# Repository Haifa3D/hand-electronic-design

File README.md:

# Oded Hand Electrical Design  

This project is a sub-project of Haifa3D Robotic Hand.
In this project, we present the electrical design of the Oded Hand – a 3D printed robotic hand with five micro-DC motors. 
The aim of this design is to be low cost, accessible, easy to assemble, robust and lightweight.  

## Design Description  
The Oded Hand can perform a variety of user-defined hand configurations using an autonomous adaptive grip along with a variety of configurable grip force levels.
The electrical design consists of four fingers with four different tendon-driven mechanisms actuated by four micro-DC motors, a passive thumb which magnetically locks in two discrete positions and wrist rotation driven by planetary gears and a DC motor. 

The electronic system consists of:
* The circuit and controller code
* The circuit housing and socket
* The batteries housing

The electronic system presented here also allows a Bluetooth communication between the Hand and your phone for settings configuration and a modular sensors control (see our [Mobile App](https://github.com/Haifa3D/haifa3d-hand-app)). For more details on how to manufacture and assemble the hand, please check out our [Mechanical Design](https://github.com/Haifa3D/hand-mechanical-design). 

## Who can benefit from this Design?  
The design is suitable for users with transradial amputation (below the elbow).
We welcome any new developers to enhance our design or to use the Oded Hand as a simulator for your new sensors/algorithms/methods that would potentially help users with controling their prosthetic hand.

## Design Files and Versions  
The STL files for the battery housing and the circuit housing can be found [here](CAD_files). The gerber files of the PCB design can be found [here](gerber_files/CAMOutputs) as well as the [schematic and layout](docs). The EAGLE files for modifying the board can be found [here](EAGLE_files). The Arduino code for the controller can be downloaded from [here](controller_software/Oded_Hand_board7_app2_4_6).

## Getting Started:
To build the electronic system for Oded Hand you will need a basic knowledge of soldering and the following componenets: 

| Component Name | Quantity | Value | links |
| --- | --- | --- | --- |
| ESP32 DEVKIT V1| 1 | - | [pinouts](https://randomnerdtutorials.com/esp32-pinout-reference-gpios/) [aliexpress](https://www.aliexpress.com/item/4000071762309.html?spm=a2g0s.9042311.0.0.64074c4du1Hh8a) |
| DRV8833 Pololu breakout board | 3 | - | [pololu](https://www.pololu.com/product/2130) | 
| micro metal dc motor | 5 | MP/LP, 100-200 RPM x 4, 30RPM x 1 | [pololu](https://www.pololu.com/product/2360), [aliexpress](https://www.aliexpress.com/item/1005003482247510.html?spm=a2g0o.productlist.main.5.70497ad7QQdXAy&algo_pvid=51493eeb-ec56-46bd-8e1c-2290c1519572&algo_exp_id=51493eeb-ec56-46bd-8e1c-2290c1519572-2&pdp_npi=3%40dis%21USD%212.08%211.44%21%21%21%21%21%40212279b716866852206383478d075c%2112000025985331271%21sea%21IL%211746261860&curPageLogUid=CFjbpVP4CzBR) | 
| IDC Connector flat cable | 1 x Right Angle Male + 1 x Female | 5x2 pins | [aliexpress RA Male](https://www.aliexpress.com/item/32841491672.html?spm=a2g0s.9042311.0.0.64074c4du1Hh8a), [aliexpress Female](https://www.aliexpress.com/item/32848157974.html?spm=a2g0s.9042311.0.0.64074c4du1Hh8a) |
| KF2510 Connector | 1 x Right Angle Male + 1 x Female  | 2 pins, 2.54mm pitch | [aliexpress](https://www.aliexpress.com/item/4000229650832.html?spm=a2g0o.productlist.0.0.580e59f7kz5W45&algo_pvid=70b8595e-d2a1-41e6-90ef-ca210f686aeb&algo_expid=70b8595e-d2a1-41e6-90ef-ca210f686aeb-20&btsid=2100bb4c16102253905804689e5410&ws_ab_test=searchweb0_0,searchweb201602_,searchweb201603_) |
| Right Angle SPDT Rocker Switch | 1 | for 3 Amp | [aliexpress](https://www.aliexpress.com/i/33009610601.html) |
| RGB LED Common Cathode | 1 | Common Cathode | [aliexpress](https://www.aliexpress.com/item/32666259962.html?spm=a2g0s.9042311.0.0.27424c4dhW29h7) |
| Li-ion 18650 battery | 2-4 | >2500mAh | [aliexpress](https://www.aliexpress.com/item/4000838767077.html?spm=a2g0o.detail.1000013.7.89c81382J9Ew7p&gps-id=pcDetailBottomMoreThisSeller&scm=1007.13339.291025.0&scm_id=1007.13339.291025.0&scm-url=1007.13339.291025.0&pvid=9ae560ff-e9e4-4dd9-a998-aac4cd26bcfe&_t=gps-id:pcDetailBottomMoreThisSeller,scm-url:1007.13339.291025.0,pvid:9ae560ff-e9e4-4dd9-a998-aac4cd26bcfe,tpp_buckets:668%232846%238116%232002&pdp_npi=3%40dis%21USD%213.75%212.62%21%21%21%21%21%402103244816864283632677463e15d8%2110000008755087021%21rec%21IL%211746261860) |
| battery Spring Contact Plate For AA AAA Battery | 4 | =< 12x12 mm |[aliexpress](https://www.aliexpress.com/item/1005001308633882.html?spm=a2g0o.detail.1000014.4.231d5d481DZZjH&gps-id=pcDetailBottomMoreOtherSeller&scm=1007.33416.205061.0&scm_id=1007.33416.205061.0&scm-url=1007.33416.205061.0&pvid=e82892c5-870e-4ffe-bb26-f0607f6946e2&_t=gps-id:pcDetailBottomMoreOtherSeller,scm-url:1007.33416.205061.0,pvid:e82892c5-870e-4ffe-bb26-f0607f6946e2,tpp_buckets:668%230%23131923%2347_668%23888%233325%235_23416%230%23205061%2320_23416%234721%2321967%23165_23416%234722%2321972%2310_668%232846%238112%231997_668%232717%237562%23468_668%231000022185%231000066059%230_668%233422%2315392%23668_4452%230%23211409%230_4452%233474%2315675%2389_4452%234862%2322449%23497_4452%233098%239599%23887_4452%235108%2323442%23113_4452%233564%2316062%236) |
| Resistors (through hole) |  | 1x2M, 1x1M, 1x10K, 2x100ohm, 1x150ohm, 5x(0.5-0.7)ohm | |

### Instructions
* send the [gerber files](gerber_files/CAMOutputs) for manufacturing at one of the availble online services (for instance, check out [PCBWay](https://www.pcbway.com/))

* order all the components from the list above.

* Cut the drv8833 according to [Pololu's instructions](https://www.pololu.com/product/2130) and check that both of the Isense pins are NOT grounded:
 
[image was taken from Pololu website]

*Tip: cut with a sharp knife the two lines, check with multimeter the resistence between AISEN/BISEN and GND. should be ~100Mohms*

* solder the headers of the drv8833 so the chip faces upward:
 
[image was taken from Pololu website]

* Solder the top side of the board (all components except the ESP32 and resistors)

*Tip: start from the led(the smallest pitch) --> drivers (drv8833)-->connectors --> button --> Switch

* Check all connections with a multimeter, to make sure everything was soldered correctly. Then cut all the pins so when you insert the esp32 controller to the bottom part nothing touches the controller. 

* Upload the [arduino code](controller_software/Oded_Hand_board7_app2_4_6) to the esp32 or an empty code, and only then solder the esp32 and the resistors (making sure there is no previous code that might cause problem to the component when it turned on). For the resistors: 1M and 2M for the voltage divider, 10K for the button, 2x100 and 1x150 ohm for the LEDs, 5x0.5ohm for the Rsense (you can use also 0.7 ohm)

After you complete the PCB assembly of Oded's Hand, please refer to the [Mechanical Design](https://github.com/Haifa3D/hand-mechanical-design) to assemble the mechanical parts of Oded's Hand. If you have already assembled the mechanical and the electrical parts, you are welcome to check out our [Mobile App](https://github.com/Haifa3D/haifa3d-hand-app) to refine the controller parameters and to define your favorite hand movements.

### **If it is the first time you are using the controller - download our [Mobile App](https://play.google.com/store/apps/details?id=com.gjung.haifa3d), connect to the hand, go to configuration and click on RESET Configuration and RESET Presets before any other action.**

## The Controller Software (Arduino code):
The code can be found [here](controller_software/Oded_Hand_board7_app2_4_6)

All installation instruction can be found in the code.

In general:

*working with Arduino IDE on ESP32:*

*https://randomnerdtutorials.com/installing-the-esp32-board-in-arduino-ide-windows-instructions/*

*Board Manager: esp32 by Espressif Systems 1.0.6~*

*Arduino IDE supported version ~1.8.15*

*install the following libraries:*

*ESP32 AnalogWrite by ERROUAGUY 0.1.0*

*ESP32 BLE Arduino Kolban/Krempa 1.0.1*

## The Circuit Housing and Socket
[Here](hand-electronic-design/CAD_files/circuit_housing), you can find the CAD of the circuit itself, the housing of the circuit top and bottom parts and the socket design we are using.
The socket is basically a flat surface which can be thermoformed and adjusted to fit the user arm. Usually the important measurements are the perimeter and length of the user's arm.

*Recommendation, merge the bottom part of the circuit housing into your socket design and print it as one part. If your socket design is based on thermoforming, heat the inner part of the socket so the bottom part of the circuit housing will not get deformed*.

To assemble the circuit housing you will need **3 x M2.5 5-8mm self tap screws** to mount the PCB to the bottom part and **2 x M2 5-6mm self tap screws** to connect the top to the bottom. To connect the hand to the socket you can use **3 x M2.5 5-8mm self tap screws** as well.

*The pictured circuit on the socket is from a previous version where we had 3 buttons on the hand instead of the mobile app for control.*

## The Batteries Housing
You can use any two connected batteries in series to power the circuit. 
To assemble your own battery pack:
* print the [batteries housing files](CAD_files/batteries_housing) (*Notice the printing orientation - the 'battery_top' should be printed so its snap is parallel to the ground*)
* make sure the batteries can slide in smoothly without getting stuck at the housing walls.
* Solder the battery Spring Contact Plate - at the 'battery-top' (the lid) the plates should be soldered to each other and at the bottom each plate should be soldered to a different wire (the maximal total current can be 2.5 amp so make sure you select a suitible wire)
* Insert the filaments to mount the contact plates to the rectangular slots at the top and bottom parts. Make sure the plates are not touching each other at the bottom part (otherwise you are going to short the batteries).
* cut the excess filaments and heat the ends (see the yellow fillaments in the image below)
* screw the bottom part to the body using two **M2 4-5mm self tap screws**
* check the connection and add a 2PIN Female KF2510 Connector to the wires.
* cut an elastic strap and sew velcro (or just buy a suitible velcro elatic strap) to fasten the Battery Pack to your upper arm. a design for backles and rings are also available at the same folder.

## So What To Do Next?
If you have developed a user interface for prosthetic hands and want to implement it on a low-cost prosthetic hand, you can communicate with our Hand in three different ways:
* if your sensors and system are on the hand and arm - you can implement your code to our controller code and solder your system to the free pins (GPIO2,12,25)
* if your system is android-based - use our [**mobile app and SDK**](https://github.com/Haifa3D/haifa3d-hand-app) to wirelessly communicate with our Hand 
* if your system is esp32-based - use the example Arduino IDE code [here](controller_software/Hand_UI_demo_BLEclient) to communicate with our Hand using the built-in BLE of the esp32 controller.
* if your system is based on Python code - use the [communication example Python code](python_communication_code/) to trigger different hand movements

## Acknowledgements:
This project was done by a group of great people and with the help and guidance of generous organizations.

*Electrical design*:  Shunit Polinsky, Yair Herbest, and Noah Bernten.

*Users Communication*: Haifa 3D – a nonprofit organization that designs and builds hands for free, founded by Yoav Medan and Yacov Malinovich.

*Resources*: The Technion - Israel Institute of Technology and special thanks to Prof. Alon Wolf and the Biorobotics and Biomechanics Lab.

## Donation:

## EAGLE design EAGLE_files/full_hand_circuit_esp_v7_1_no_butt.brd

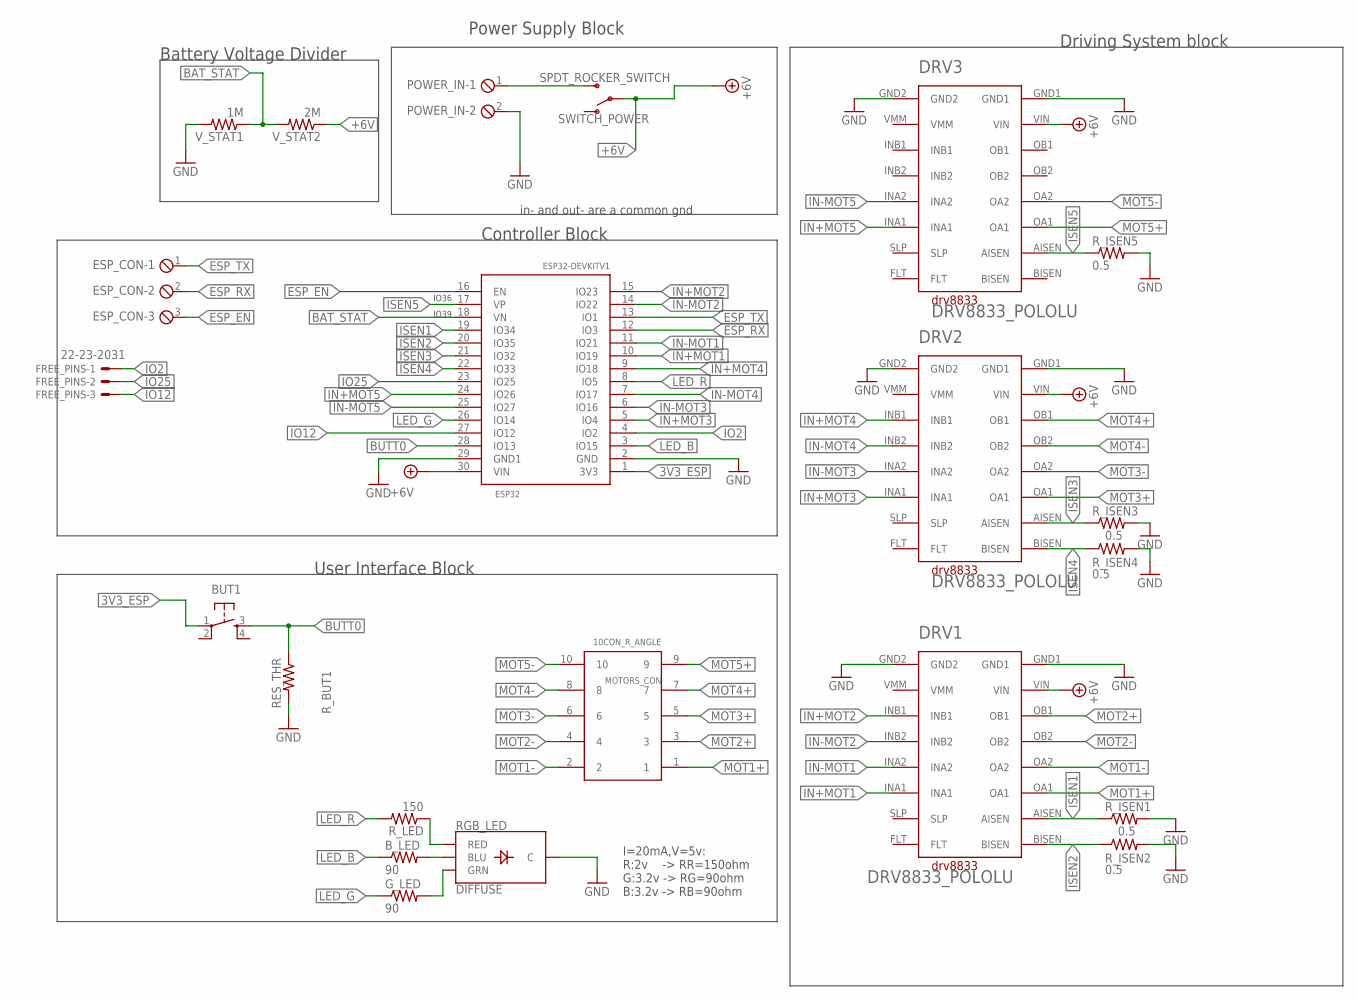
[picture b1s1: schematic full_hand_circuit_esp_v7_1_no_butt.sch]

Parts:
BUT1: PUSH_BUTTON; B3F-40XX
B_LED: 90; R_THR
DRV1, DRV2, DRV3: DRV8833_POLOLU
ESP32: ESP32DEVKITV1; ESP32-DEVKITV1
ESP_CON: MPT3; 3POL254
FREE_PINS: 22-23-2031
G_LED: 90; R_THR
MOTORS_CON: 10CON_R_ANGLE; CON10_R_ANGLE
POWER_IN: MPT2; 2POL254
RGB_LED: DIFFUSE; LED-RGB-THRU
R_BUT1: RES_THR; R_THR
R_ISEN1, R_ISEN2, R_ISEN3, R_ISEN4, R_ISEN5: 0.5; R_THR
R_LED: 150; R_THR
SWITCH_POWER: SPDT_ROCKER_SWITCH; SWITCH_SPDT_PTH_11.6X4.0MM
V_STAT1: 1M; R_THR
V_STAT2: 2M; R_THR

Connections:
3V3_ESP: BUT1.1, ESP32.1 (3V3)
+6V: DRV1.VIN, DRV2.VIN, DRV3.VIN, ESP32.30 (VIN), SWITCH_POWER.2, V_STAT2.1
BAT_STAT: ESP32.18 (VN), V_STAT1.1, V_STAT2.2
BLUE: B_LED.2, RGB_LED.4 (BLU)
BUTT0: BUT1.3 (S), ESP32.28 (IO13), R_BUT1.1
ESP_EN: ESP32.16 (EN), ESP_CON.3
ESP_RX: ESP32.12 (IO3), ESP_CON.2
ESP_TX: ESP32.13 (IO1), ESP_CON.1
GND: DRV1.GND1, DRV1.GND2, DRV2.GND1, DRV2.GND2, DRV3.GND1, DRV3.GND2, ESP32.2 (GND), ESP32.29 (GND1), POWER_IN.2, RGB_LED.2 (C), R_BUT1.2, R_ISEN1.2, R_ISEN2.2, R_ISEN3.2, R_ISEN4.2, R_ISEN5.2, V_STAT1.2
GREEN: G_LED.2, RGB_LED.3 (GRN)
IN+MOT1: DRV1.INA1, ESP32.10 (IO19)
IN+MOT2: DRV1.INB1, ESP32.15 (IO23)
IN+MOT3: DRV2.INA1, ESP32.5 (IO4)
IN+MOT4: DRV2.INB1, ESP32.9 (IO18)
IN+MOT5: DRV3.INA1, ESP32.24 (IO26)
IN-MOT1: DRV1.INA2, ESP32.11 (IO21)
IN-MOT2: DRV1.INB2, ESP32.14 (IO22)
IN-MOT3: DRV2.INA2, ESP32.6 (IO16)
IN-MOT4: DRV2.INB2, ESP32.7 (IO17)
IN-MOT5: DRV3.INA2, ESP32.25 (IO27)
IN_HIGH: POWER_IN.1, SWITCH_POWER.3 (S)
IO2: ESP32.4 (IO2), FREE_PINS.1
IO12: ESP32.27 (IO12), FREE_PINS.3
IO25: ESP32.23 (IO25), FREE_PINS.2
ISEN1: DRV1.AISEN, ESP32.19 (IO34), R_ISEN1.1
ISEN2: DRV1.BISEN, ESP32.20 (IO35), R_ISEN2.1
ISEN3: DRV2.AISEN, ESP32.21 (IO32), R_ISEN3.1
ISEN4: DRV2.BISEN, ESP32.22 (IO33), R_ISEN4.1
ISEN5: DRV3.AISEN, ESP32.17 (VP), R_ISEN5.1
LED_B: B_LED.1, ESP32.3 (IO15)
LED_G: ESP32.26 (IO14), G_LED.1
LED_R: ESP32.8 (IO5), R_LED.2
MOT1+: DRV1.OA1, MOTORS_CON.1
MOT1-: DRV1.OA2, MOTORS_CON.2
MOT2+: DRV1.OB1, MOTORS_CON.3
MOT2-: DRV1.OB2, MOTORS_CON.4
MOT3+: DRV2.OA1, MOTORS_CON.5
MOT3-: DRV2.OA2, MOTORS_CON.6
MOT4+: DRV2.OB1, MOTORS_CON.7
MOT4-: DRV2.OB2, MOTORS_CON.8
MOT5+: DRV3.OA1, MOTORS_CON.9
MOT5-: DRV3.OA2, MOTORS_CON.10
RED: RGB_LED.1 (RED), R_LED.1

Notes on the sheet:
Driving System block
I=20mA,V=5v: R:2v -> RR=150ohm G:3.2v -> RG=90ohm B:3.2v -> RB=90ohm
Controller Block
IO36
IO39
Power Supply Block
in- and out- are a common gnd
User Interface Block
Battery Voltage Divider

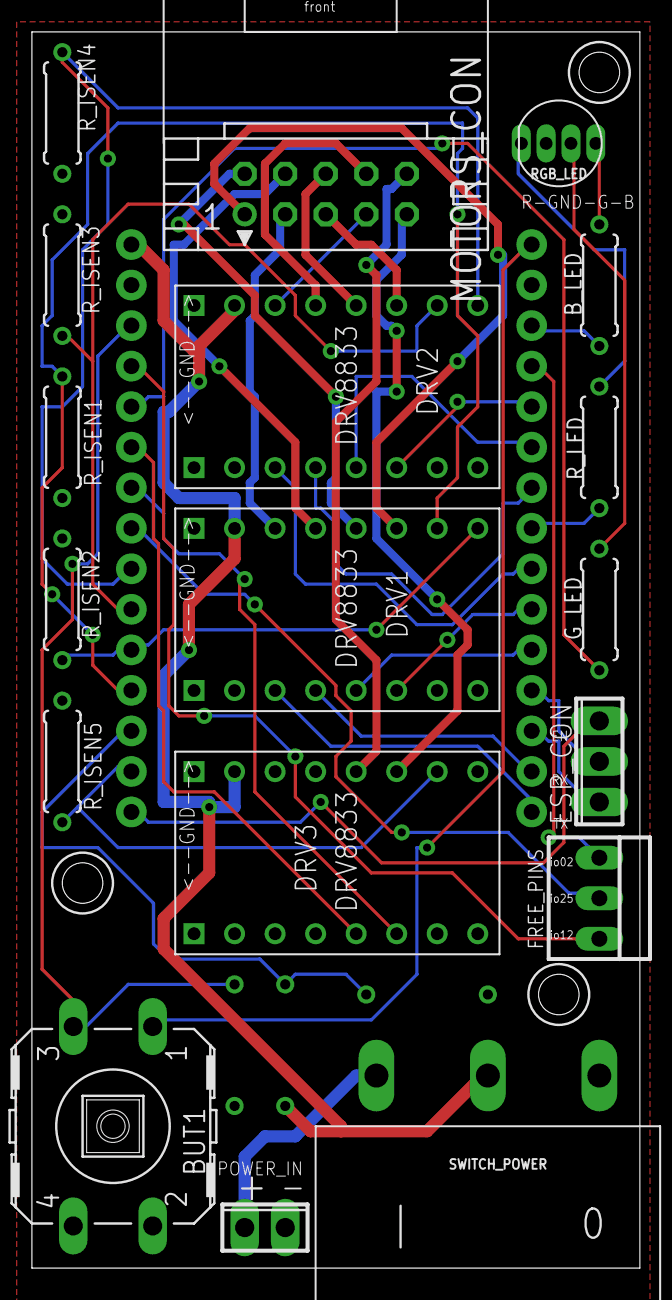
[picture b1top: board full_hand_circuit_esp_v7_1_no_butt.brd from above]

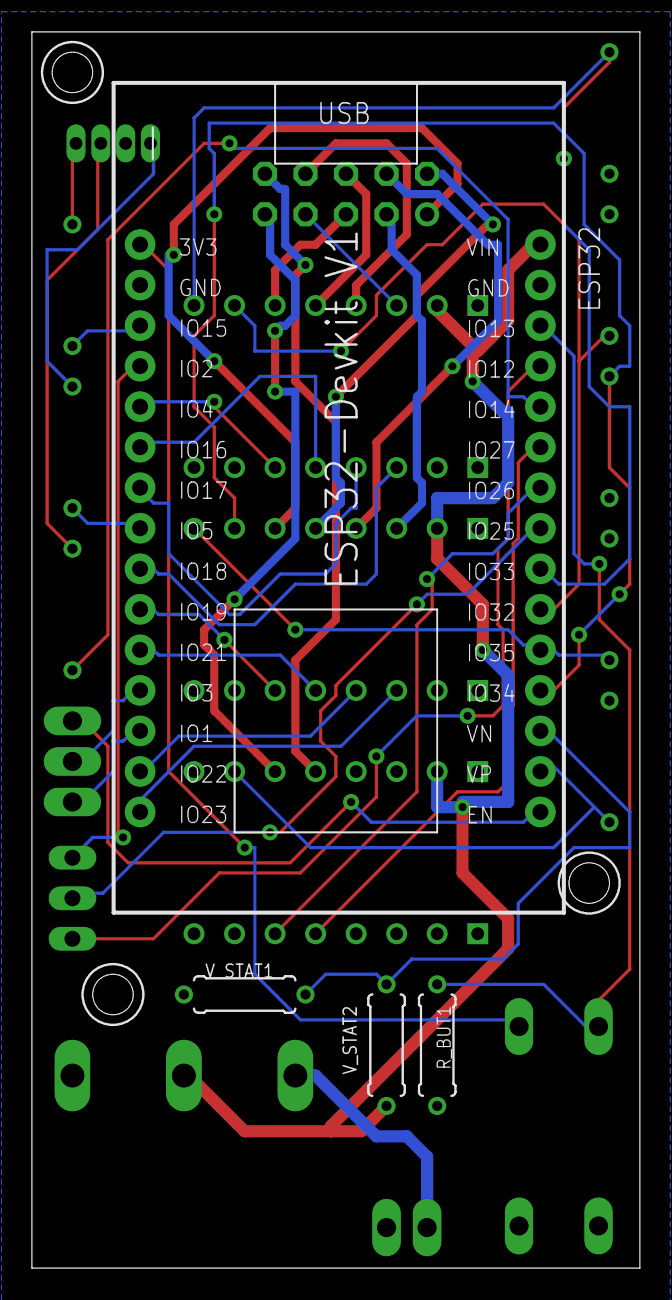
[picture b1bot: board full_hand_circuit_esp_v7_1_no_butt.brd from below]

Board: 2 copper layers, 38.1 x 77.5 mm, 22 parts (4 on the bottom side), 43 nets.

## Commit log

2021-05-11 Rename main.py to Hand_UI_demo_python.py
2021-09-07 update battery check function
2024-06-27 Add files via upload
    add more comments for smooth installation process
2024-08-31 Change license to Non-Profit Open Software License (“Non-Profit OSL”) 3.0
